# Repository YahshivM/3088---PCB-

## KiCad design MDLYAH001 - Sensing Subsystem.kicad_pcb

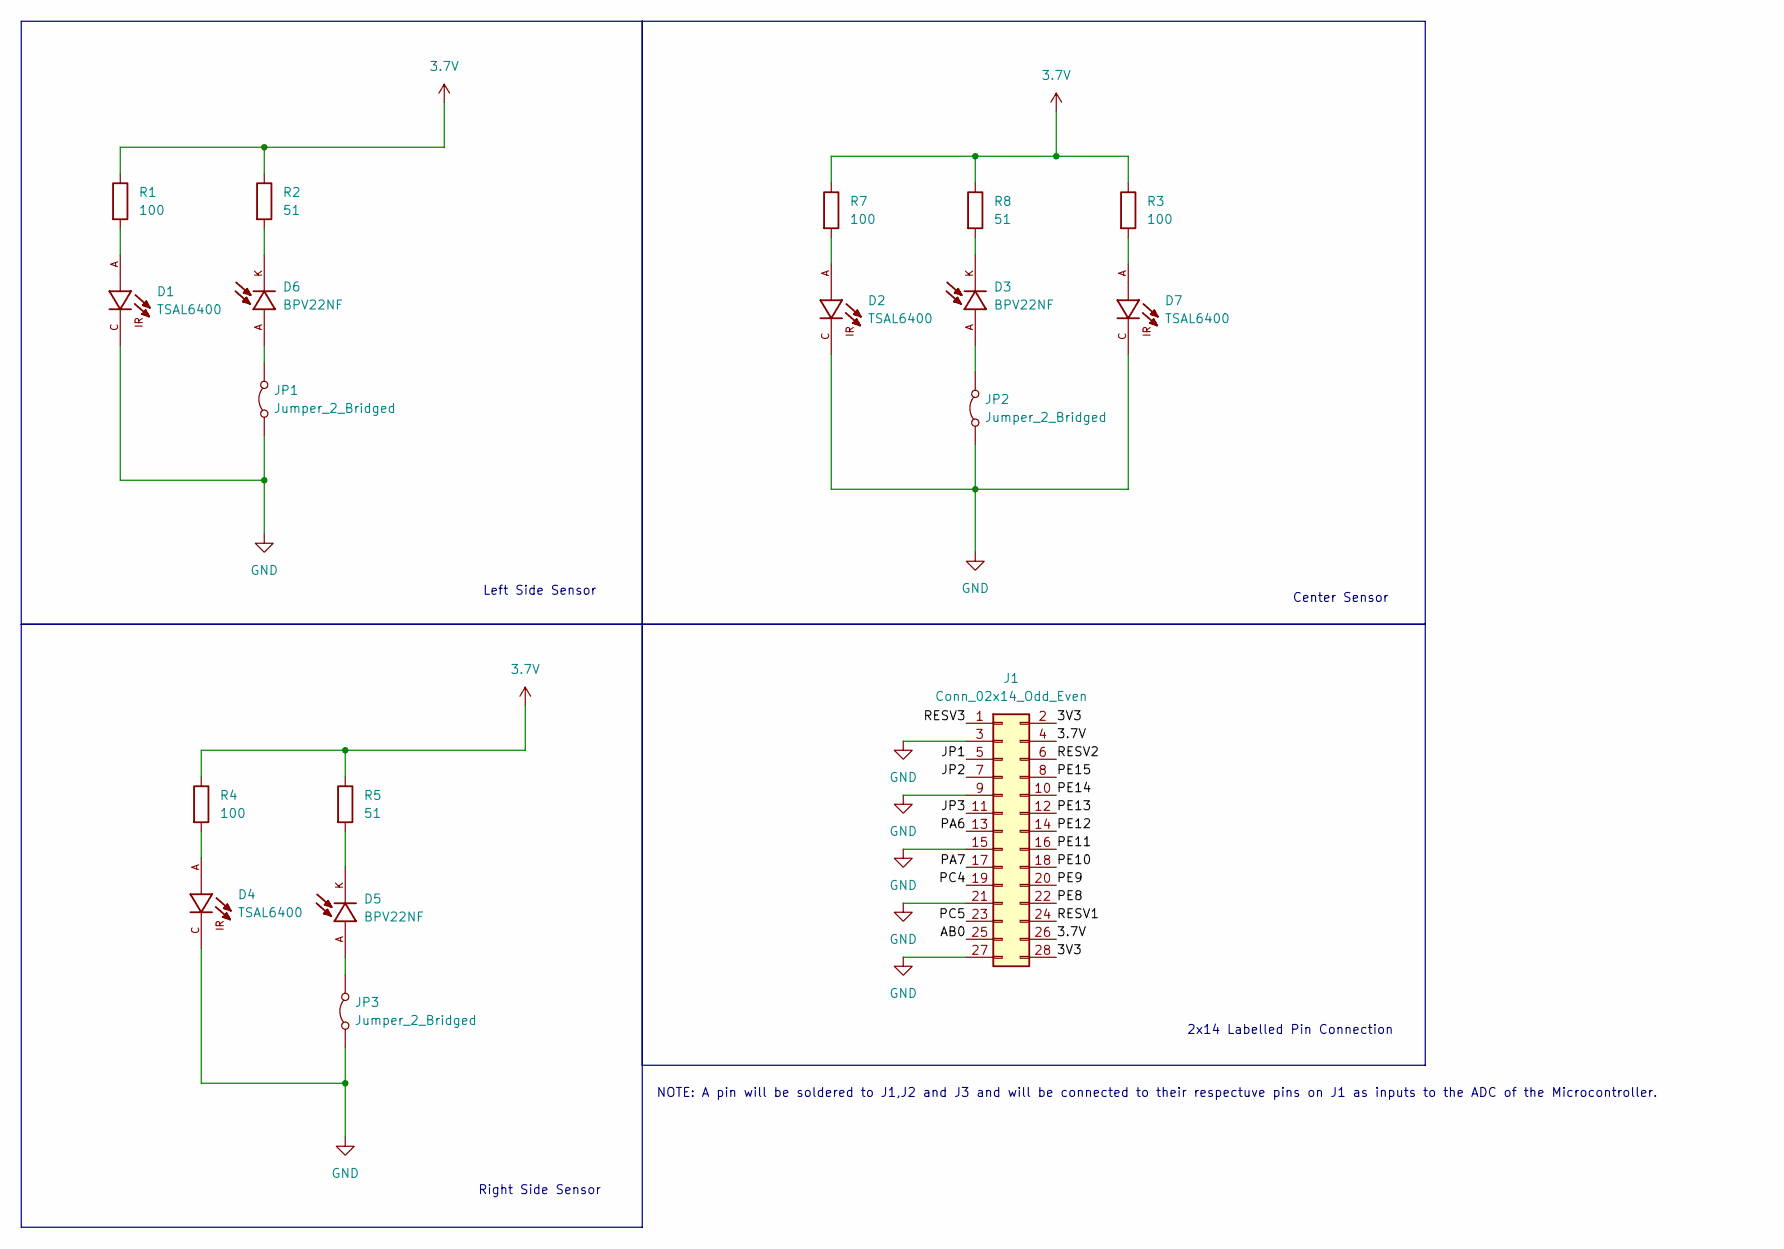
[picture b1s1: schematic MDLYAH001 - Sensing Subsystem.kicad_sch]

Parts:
D1, D2, D4, D7: TSAL6400; LEDRD254W55D595H900; PARTREV 2.0
D3, D5, D6: BPV22NF; XDCR_BPV22NF; PARTREV 1.9
J1: Conn_02x14_Odd_Even; PinHeader_2x14_P2.54mm_Vertical
JP1, JP2, JP3: Jumper_2_Bridged; SolderJumper-2_P1.3mm_Bridged2Bar_Pad1.0x1.5mm
R1, R3, R4, R7: 100; R_Axial_DIN0204_L3.6mm_D1.6mm_P1.90mm_Vertical
R2, R5, R8: 51; R_Axial_DIN0204_L3.6mm_D1.6mm_P1.90mm_Vertical

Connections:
3.7V: J1.4, J1.26, R1.1, R2.1, R3.1, R4.1, R5.1, R7.1, R8.1
/3V3: J1.2, J1.28
/AB0: J1.25
/JP1: J1.5
/JP2: J1.7
/JP3: J1.11
/PA6: J1.13
/PA7: J1.17
/PC4: J1.19
/PC5: J1.23
/PE8: J1.22
/PE9: J1.20
/PE10: J1.18
/PE11: J1.16
/PE12: J1.14
/PE13: J1.12
/PE14: J1.10
/PE15: J1.8
/RESV1: J1.24
/RESV2: J1.6
/RESV3: J1.1
GND: D1.C, D2.C, D4.C, D7.C, J1.3, J1.9, J1.15, J1.21, J1.27, JP1.1 (A), JP2.1 (A), JP3.1 (A)
unnamed: D1.A, R1.2
unnamed: D2.A, R7.2
unnamed: D3.K, R8.2
unnamed: D4.A, R4.2
unnamed: D5.K, R5.2
unnamed: D6.K, R2.2
unnamed: D7.A, R3.2
unnamed: D6.A, JP1.2 (B)
unnamed: D3.A, JP2.2 (B)
unnamed: D5.A, JP3.2 (B)

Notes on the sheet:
2x14 Labelled Pin Connection
NOTE: A pin will be soldered to J1,J2 and J3 and will be connected to their respectuve pins on J1 as inputs to the ADC of the Microcontroller.
Right Side Sensor
Center Sensor
Left Side Sensor

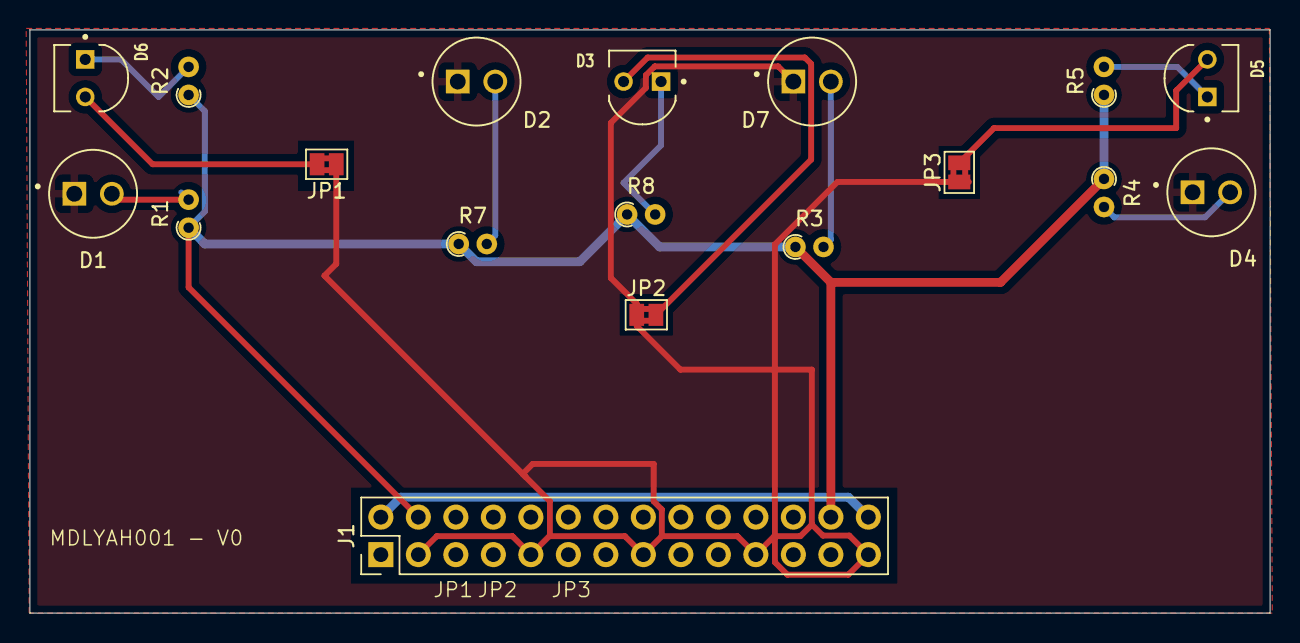
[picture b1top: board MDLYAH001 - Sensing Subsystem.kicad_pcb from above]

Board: 2 copper layers, 84.0 x 39.5 mm, 18 parts (0 on the bottom side), 13 nets.

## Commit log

2024-03-16 Project Brief
